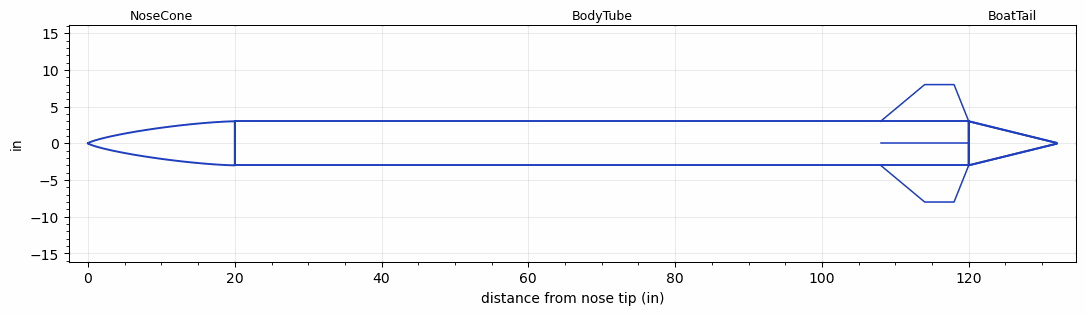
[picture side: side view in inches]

<RASAeroDocument>
 <FileVersion>2</FileVersion>
 <RocketDesign>
  <NoseCone>
   <Length>20</Length>
   <Diameter>6</Diameter>
   <Shape>Von Karman Ogive</Shape>
   <BluntRadius>0.1</BluntRadius>
   <Location>0</Location>
  </NoseCone>
  <BodyTube>
   <Length>100</Length>
   <Diameter>6</Diameter>
   <Location>20</Location>
   <BoattailLength>12</BoattailLength>
   <BoattailRearDiameter>0.1</BoattailRearDiameter>
   <Fin>
    <Count>4</Count>
    <Chord>12</Chord>
    <Span>5</Span>
    <SweepDistance>6</SweepDistance>
    <TipChord>4</TipChord>
    <Thickness>0.125</Thickness>
    <LERadius>0.01</LERadius>
    <Location>12</Location>
    <AirfoilSection>Biconvex</AirfoilSection>
   </Fin>
   <Protuberance>
    <StreamlinedNoBaseDrag>0</StreamlinedNoBaseDrag>
    <StreamlinedWithBaseDrag>19.476</StreamlinedWithBaseDrag>
    <InclinedPlate1Angle>0</InclinedPlate1Angle>
    <InclinedPlate1FrontalArea>0</InclinedPlate1FrontalArea>
    <InclinedPlate2Angle>0</InclinedPlate2Angle>
    <InclinedPlate2FrontalArea>0</InclinedPlate2FrontalArea>
   </Protuberance>
  </BodyTube>
  <BoatTail>
   <Length>12</Length>
   <Diameter>6</Diameter>
   <RearDiameter>0.1</RearDiameter>
   <Location>120</Location>
  </BoatTail>
  <Surface>Smooth Paint</Surface>
  <ModifiedBarrowman>True</ModifiedBarrowman>
  <Turbulence>True</Turbulence>
  <UseBooster1>False</UseBooster1>
  <UseBooster2>False</UseBooster2>
 </RocketDesign>
 <LaunchSite>
  <Altitude>800</Altitude>
  <Pressure>0</Pressure>
  <RodAngle>0</RodAngle>
  <RodLength>12</RodLength>
  <Temperature>85</Temperature>
  <WindSpeed>0</WindSpeed>
 </LaunchSite>
 <Recovery>
  <Altitude1>1000</Altitude1>
  <Altitude2>1000</Altitude2>
  <DeviceType1>Parachute</DeviceType1>
  <DeviceType2>None</DeviceType2>
  <Event1>False</Event1>
  <Event2>False</Event2>
  <Size1>0</Size1>
  <Size2>1</Size2>
  <EventType1>Apogee</EventType1>
  <EventType2>None</EventType2>
  <CD1>0</CD1>
  <CD2>1.33</CD2>
 </Recovery>
 <SimulationList>
  <Simulation>
   <SustainerEngine>R100000000  (C-Dog)</SustainerEngine>
   <SustainerLaunchWt>150</SustainerLaunchWt>
   <SustainerNozzleDiameter>4</SustainerNozzleDiameter>
   <SustainerCG>48</SustainerCG>
   <SustainerIgnitionDelay>0</SustainerIgnitionDelay>
   <Booster1SeparationDelay>0</Booster1SeparationDelay>
   <Booster1IgnitionDelay>0</Booster1IgnitionDelay>
   <IncludeBooster1>False</IncludeBooster1>
   <Booster2Delay>0</Booster2Delay>
   <IncludeBooster2>False</IncludeBooster2>
   <TimetoApogee>91.48113</TimetoApogee>
   <MaxAltitude>135900.9</MaxAltitude>
   <MaxVelocity>3544.952</MaxVelocity>
  </Simulation>
  <Simulation>
   <SustainerEngine>O6000W  (AeroTech)</SustainerEngine>
   <SustainerLaunchWt>125</SustainerLaunchWt>
   <SustainerNozzleDiameter>4</SustainerNozzleDiameter>
   <SustainerCG>40</SustainerCG>
   <SustainerIgnitionDelay>0</SustainerIgnitionDelay>
   <Booster1SeparationDelay>0</Booster1SeparationDelay>
   <Booster1IgnitionDelay>0</Booster1IgnitionDelay>
   <IncludeBooster1>False</IncludeBooster1>
   <Booster2Delay>0</Booster2Delay>
   <IncludeBooster2>False</IncludeBooster2>
   <TimetoApogee>88.70054</TimetoApogee>
   <MaxAltitude>125850.8</MaxAltitude>
   <MaxVelocity>3573.073</MaxVelocity>
  </Simulation>
 </SimulationList>
</RASAeroDocument>
